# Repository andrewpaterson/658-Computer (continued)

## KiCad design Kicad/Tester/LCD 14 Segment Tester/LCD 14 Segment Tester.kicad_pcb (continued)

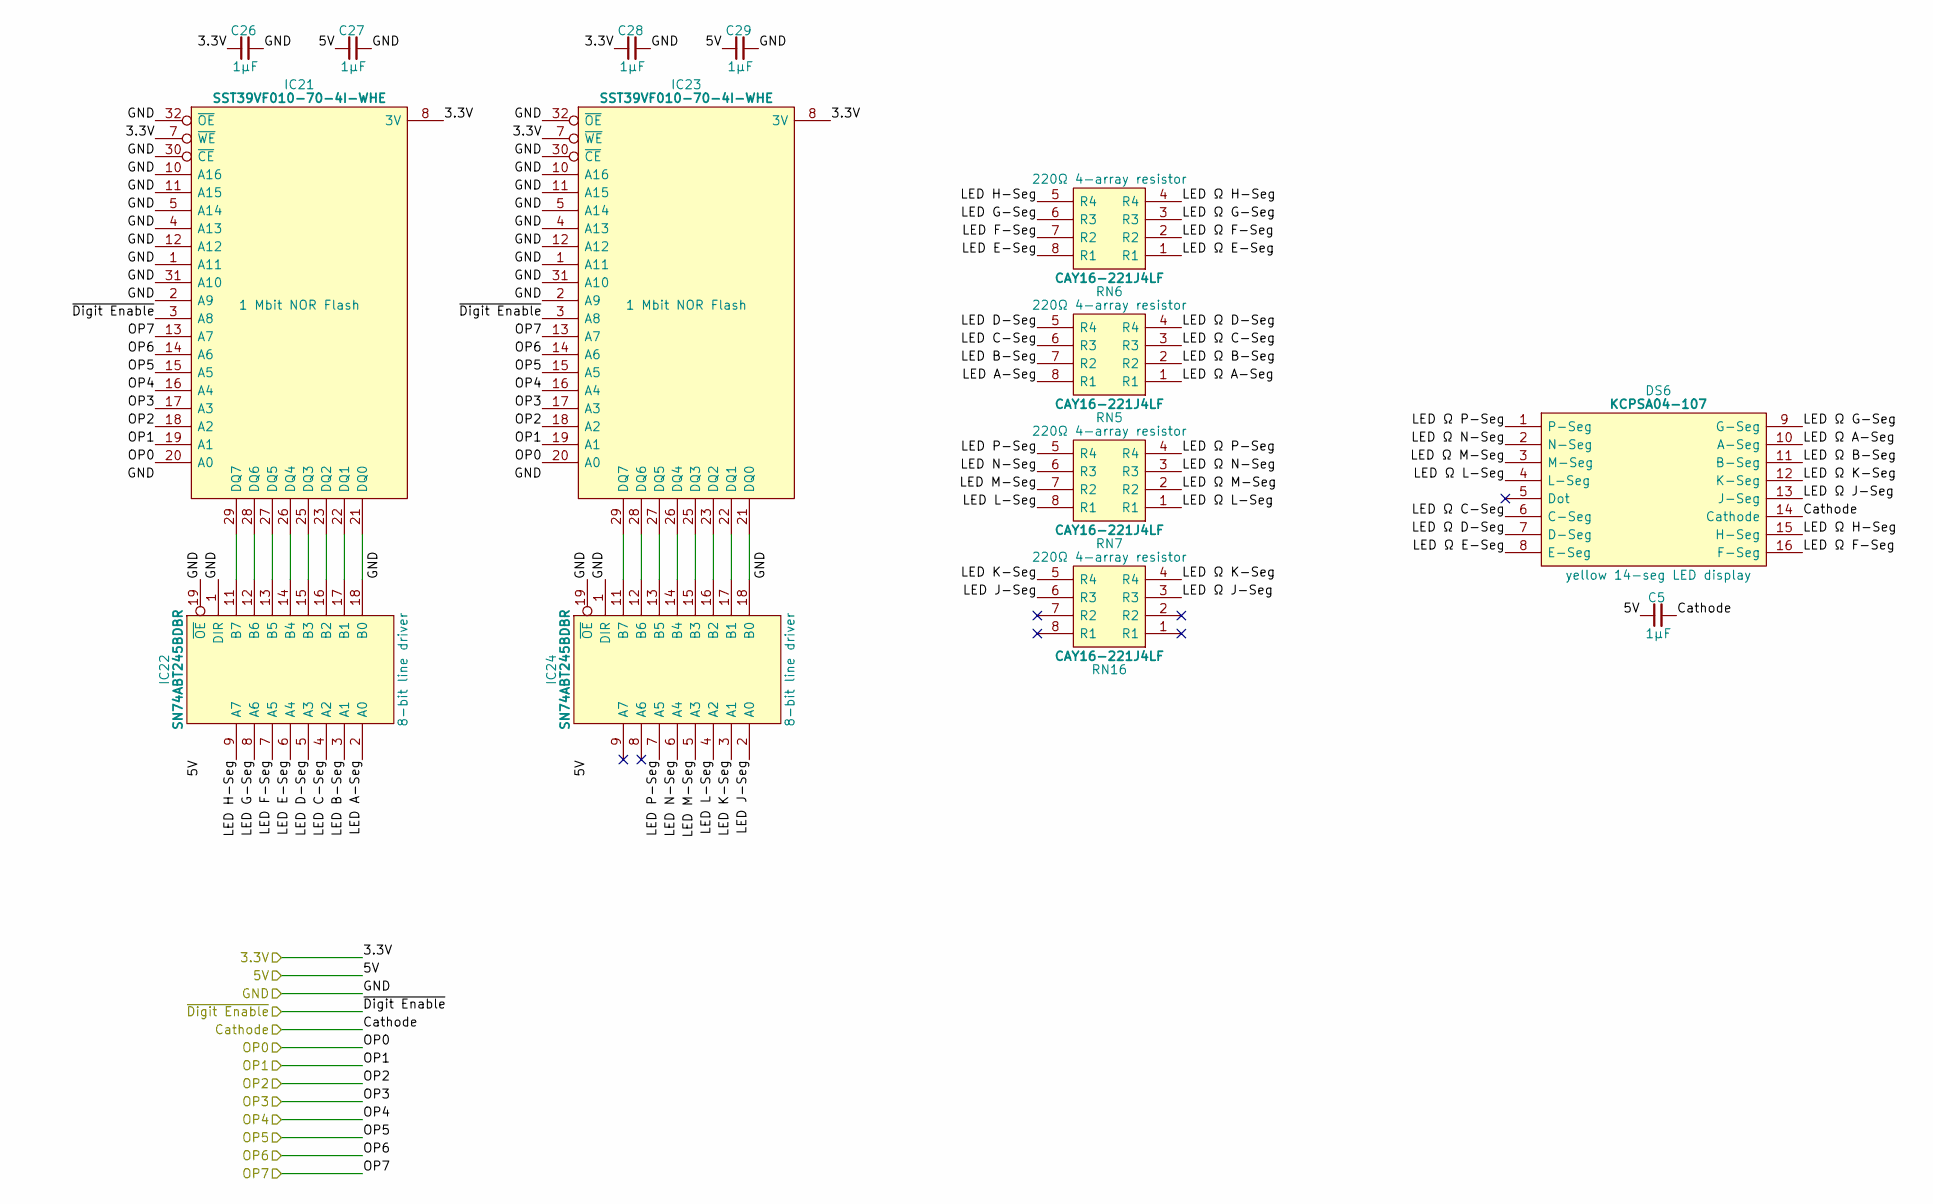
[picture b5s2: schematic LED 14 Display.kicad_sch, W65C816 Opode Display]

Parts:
C5, C26, C27, C28, C29: 1μF; C_0805
DS6: KCPSA04-107; KCPSA04107; Manufacturer_Part_Number KCPSA04-107; Mouser Part Number N/A
IC21, IC23: SST39VF010-70-4I-WHE; DIP-32_TSSOP_14mm_Adapter; Manufacturer_Part_Number SST39VF010-70-4I-WHE-T; Mouser Part Number 579-39VF0107IWHET
IC22, IC24: SN74ABT245BDBR; SOP65P780X200-20N; Manufacturer_Part_Number SN74ABT245BDBR; Mouser Part Number 595-SN74ABT245BDBR
RN5, RN6, RN7, RN16: CAY16-221J4LF; CAY16-F4; Manufacturer_Part_Number CAY16-221J4LF; Mouser Part Number 652-CAY16-221J4LF

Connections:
/3.3V: C26.1, C28.1, IC21.7 (~WE), IC21.8 (3V), IC23.7 (~WE), IC23.8 (3V); also elsewhere on the board
/5V: C5.1, C27.1, C29.1, IC22.20 (5V), IC24.20 (5V); also elsewhere on the board
/GND: C5.2, C26.2, C27.2, C28.2, C29.2, DS6.14 (Cathode), IC21.1 (A11), IC21.2 (A9), IC21.3 (A8), IC21.4 (A13), IC21.5 (A14), IC21.10 (A16), IC21.11 (A15), IC21.12 (A12), IC21.24 (GND), IC21.30 (~CE), IC21.31 (A10), IC21.32 (~OE), IC22.1 (DIR), IC22.10 (GND), IC22.19 (~OE), IC23.1 (A11), IC23.2 (A9), IC23.3 (A8), IC23.4 (A13), IC23.5 (A14), IC23.10 (A16), IC23.11 (A15), IC23.12 (A12), IC23.24 (GND), IC23.30 (~CE), IC23.31 (A10), IC23.32 (~OE), IC24.1 (DIR), IC24.10 (GND), IC24.19 (~OE); also elsewhere on the board
/Left Opcode/LED A-Seg: IC22.2 (A0), RN5.8 (R1)
/Left Opcode/LED B-Seg: IC22.3 (A1), RN5.7 (R2)
/Left Opcode/LED C-Seg: IC22.4 (A2), RN5.6 (R3)
/Left Opcode/LED D-Seg: IC22.5 (A3), RN5.5 (R4)
/Left Opcode/LED E-Seg: IC22.6 (A4), RN6.8 (R1)
/Left Opcode/LED F-Seg: IC22.7 (A5), RN6.7 (R2)
/Left Opcode/LED G-Seg: IC22.8 (A6), RN6.6 (R3)
/Left Opcode/LED H-Seg: IC22.9 (A7), RN6.5 (R4)
/Left Opcode/LED J-Seg: IC24.2 (A0), RN16.6 (R3)
/Left Opcode/LED K-Seg: IC24.3 (A1), RN16.5 (R4)
/Left Opcode/LED L-Seg: IC24.4 (A2), RN7.8 (R1)
/Left Opcode/LED M-Seg: IC24.5 (A3), RN7.7 (R2)
/Left Opcode/LED N-Seg: IC24.6 (A4), RN7.6 (R3)
/Left Opcode/LED P-Seg: IC24.7 (A5), RN7.5 (R4)
/Left Opcode/LED Ω A-Seg: DS6.10 (A-Seg), RN5.1 (R1)
/Left Opcode/LED Ω B-Seg: DS6.11 (B-Seg), RN5.2 (R2)
/Left Opcode/LED Ω C-Seg: DS6.6 (C-Seg), RN5.3 (R3)
/Left Opcode/LED Ω D-Seg: DS6.7 (D-Seg), RN5.4 (R4)
/Left Opcode/LED Ω E-Seg: DS6.8 (E-Seg), RN6.1 (R1)
/Left Opcode/LED Ω F-Seg: DS6.16 (F-Seg), RN6.2 (R2)
/Left Opcode/LED Ω G-Seg: DS6.9 (G-Seg), RN6.3 (R3)
/Left Opcode/LED Ω H-Seg: DS6.15 (H-Seg), RN6.4 (R4)
/Left Opcode/LED Ω J-Seg: DS6.13 (J-Seg), RN16.3 (R3)
/Left Opcode/LED Ω K-Seg: DS6.12 (K-Seg), RN16.4 (R4)
/Left Opcode/LED Ω L-Seg: DS6.4 (L-Seg), RN7.1 (R1)
/Left Opcode/LED Ω M-Seg: DS6.3 (M-Seg), RN7.2 (R2)
/Left Opcode/LED Ω N-Seg: DS6.2 (N-Seg), RN7.3 (R3)
/Left Opcode/LED Ω P-Seg: DS6.1 (P-Seg), RN7.4 (R4)
unnamed: IC21.21 (DQ0), IC22.18 (B0)
unnamed: IC21.22 (DQ1), IC22.17 (B1)
unnamed: IC21.23 (DQ2), IC22.16 (B2)
unnamed: IC21.25 (DQ3), IC22.15 (B3)
unnamed: IC21.26 (DQ4), IC22.14 (B4)
unnamed: IC21.27 (DQ5), IC22.13 (B5)
unnamed: IC21.28 (DQ6), IC22.12 (B6)
unnamed: IC21.29 (DQ7), IC22.11 (B7)
unnamed: IC23.21 (DQ0), IC24.18 (B0)
unnamed: IC23.22 (DQ1), IC24.17 (B1)
unnamed: IC23.23 (DQ2), IC24.16 (B2)
unnamed: IC23.25 (DQ3), IC24.15 (B3)
unnamed: IC23.26 (DQ4), IC24.14 (B4)
unnamed: IC23.27 (DQ5), IC24.13 (B5)
unnamed: IC23.28 (DQ6), IC24.12 (B6)
unnamed: IC23.29 (DQ7), IC24.11 (B7)
OP0: IC21.20 (A0), IC23.20 (A0); also elsewhere on the board
OP1: IC21.19 (A1), IC23.19 (A1); also elsewhere on the board
OP2: IC21.18 (A2), IC23.18 (A2); also elsewhere on the board
OP3: IC21.17 (A3), IC23.17 (A3); also elsewhere on the board
OP4: IC21.16 (A4), IC23.16 (A4); also elsewhere on the board
OP5: IC21.15 (A5), IC23.15 (A5); also elsewhere on the board
OP6: IC21.14 (A6), IC23.14 (A6); also elsewhere on the board
OP7: IC21.13 (A7), IC23.13 (A7); also elsewhere on the board

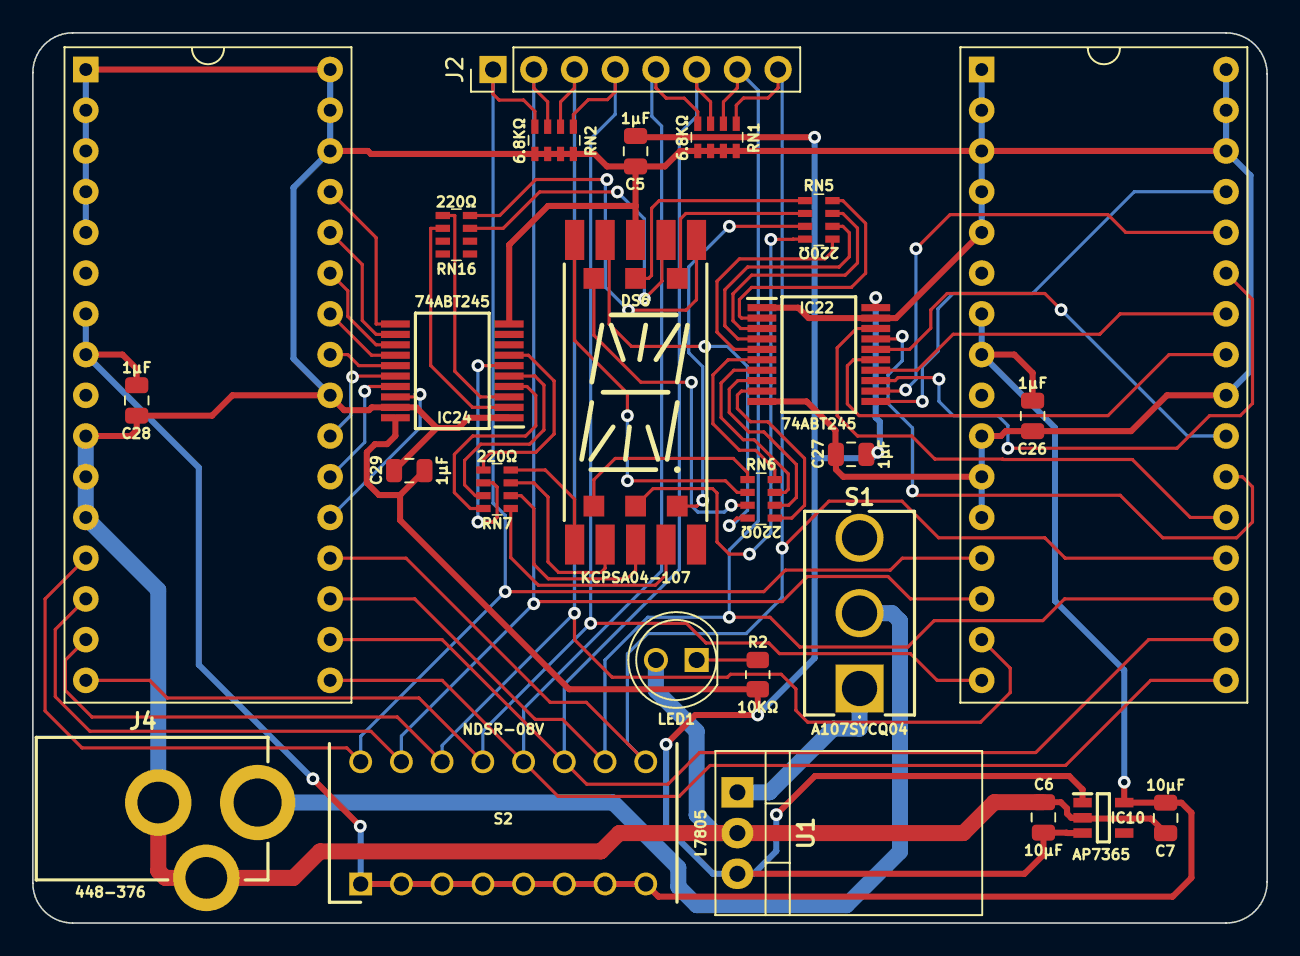
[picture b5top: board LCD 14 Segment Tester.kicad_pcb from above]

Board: 2 copper layers, 77.0 x 55.5 mm, 26 parts (0 on the bottom side), 58 nets.

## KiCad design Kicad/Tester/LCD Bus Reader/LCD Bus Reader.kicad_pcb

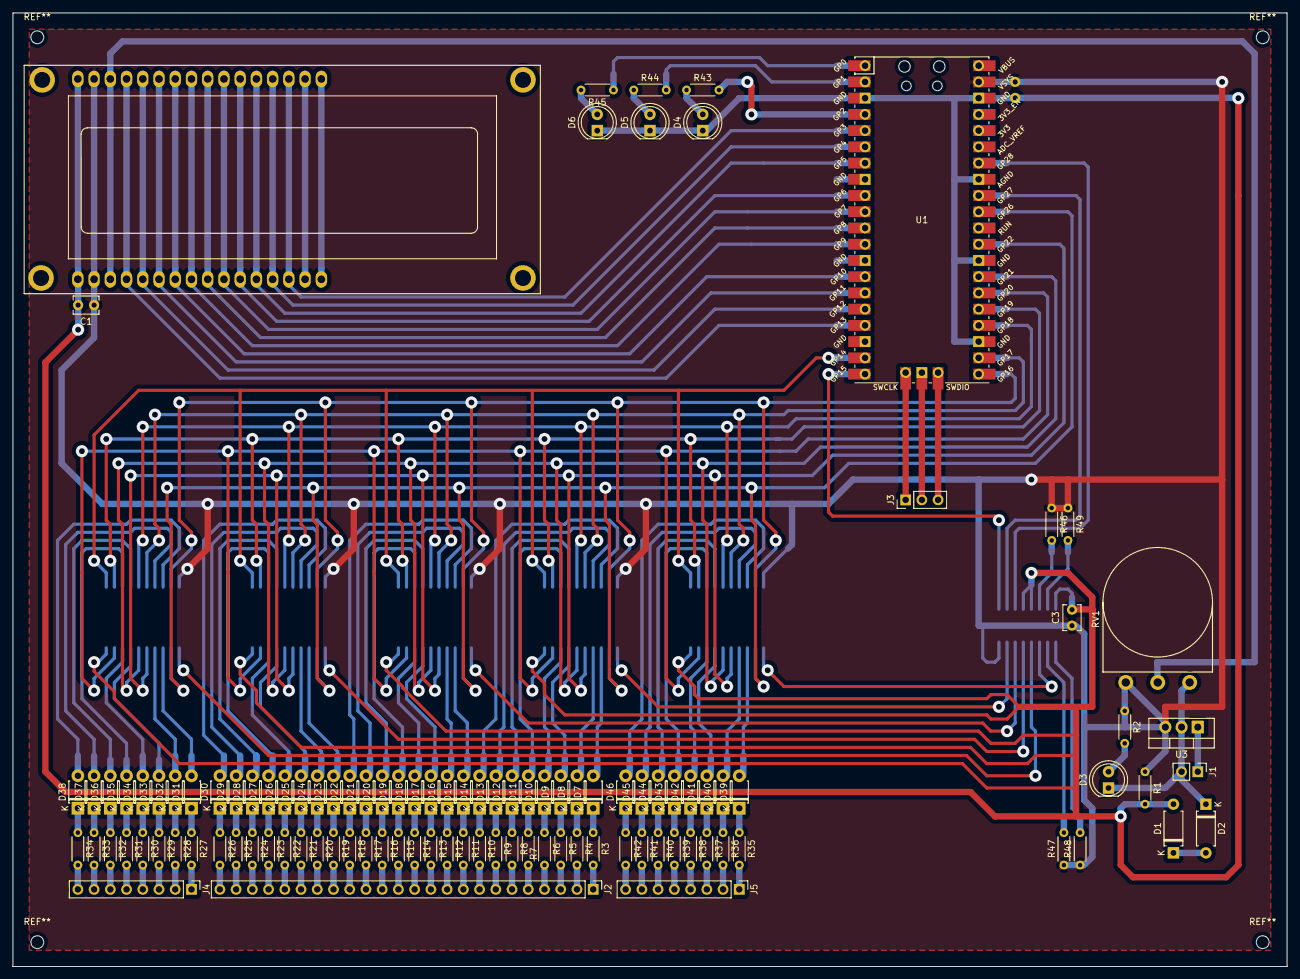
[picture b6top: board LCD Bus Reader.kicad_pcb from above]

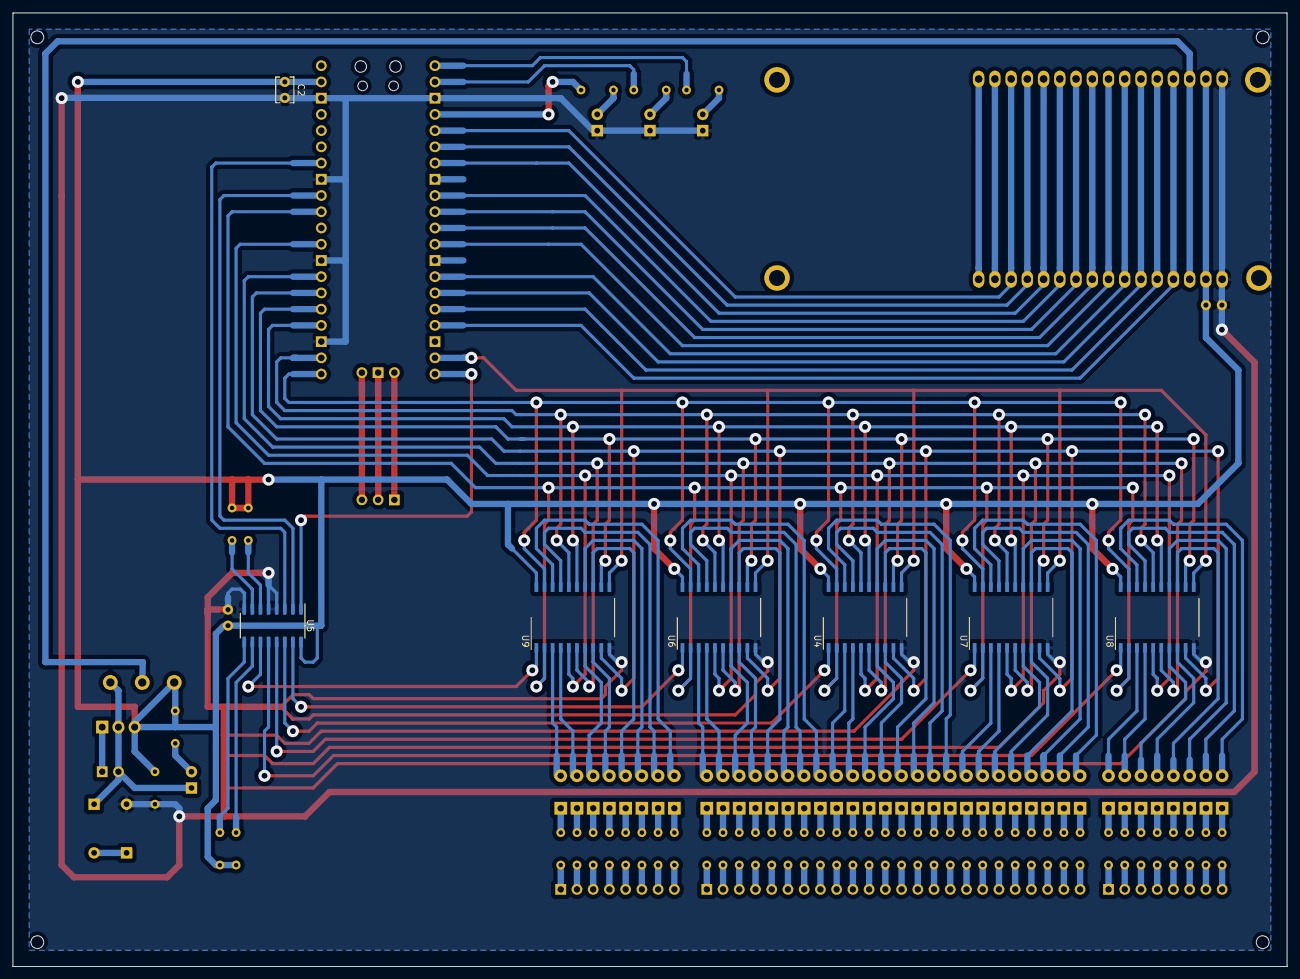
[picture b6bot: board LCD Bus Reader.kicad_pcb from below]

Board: 2 copper layers, 199.4 x 149.2 mm, 113 parts (7 on the bottom side), 168 nets.

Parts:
C1, C2, C3: C; C_Disc_D3.8mm_W2.6mm_P2.50mm
D1, D2: D_Zener; D_A-405_P7.62mm_Horizontal
D3, D4, D5, D6: LED; LED_D5.0mm
D7, D8, D9, D10, D11, D12, D13, D14, D15, D16, D17, D18, D19, D20, D21, D22, D23, D24, D25, D26, D27, D28, D29, D30, D31, D32, D33, D34, D35, D36, D37, D38, D39, D40, D41, D42, D43, D44, D45, D46: 1N4148; D_T-1_P5.08mm_Horizontal
J1: Conn_01x02_Male; PinHeader_1x02_P2.54mm_Vertical
J2: Conn_01x24_Male; PinHeader_1x24_P2.54mm_Vertical
J3: Conn_01x03_Male; PinHeader_1x03_P2.54mm_Vertical
J4, J5: Conn_01x08_Male; PinHeader_1x08_P2.54mm_Vertical
R1, R2, R3, R4, R5, R6, R7, R8, R9, R10, R11, R12, R13, R14, R15, R16, R17, R18, R19, R20, R21, R22, R23, R24, R25, R26, R27, R28, R29, R30, R31, R32, R33, R34, R35, R36, R37, R38, R39, R40, R41, R42, R43, R44, R45, R46, R47, R48, R49: R; R_Axial_DIN0204_L3.6mm_D1.6mm_P5.08mm_Horizontal
RV1: R_POT; Potentiometer_Omeg_PC16BU_Vertical
U1: Pico; RPi_Pico_SMD_TH
U2: RC1602A; NMTC-S16205
U3: L7805; TO-220-3_Vertical
U4, U6, U7, U8, U9: 74LS373; SO-20_12.8x7.5mm_P1.27mm
U5: 74LS138; SO-16_3.9x9.9mm_P1.27mm

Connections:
+12V: J1.1, U3.1
/0V: D2.1, D3.1, J1.2, RV1.1, U3.2
/1.6V: C1.2, C2.2, C3.2, D1.2, D4.1, D5.1, D6.1, R1.2, U1.3, U1.23, U1.28, U1.33, U1.38, U2.1, U4.10, U5.4, U5.5, U5.8, U6.10, U7.10, U8.10, U9.10
/5V: C1.1, C2.1, C3.1, R1.1, R2.1, R46.1, R47.1, R48.1, R49.1, RV1.3, U1.39, U2.2, U3.3, U4.20, U5.16, U6.20, U7.20, U8.20, U9.20
/CE0: U5.15, U6.1
/CE1: U4.1, U5.14
/CE2: U5.13, U7.1
/CE3: U5.12, U8.1
/CE4: U5.11, U9.1
/CE5: R47.2, U5.10
/CE6: R48.2, U5.9
/CE7: R49.2, U5.7
/CS0: U1.20, U5.1
/CS1: U1.32, U5.2
/CS2: U1.34, U5.3
/DB0: U1.14, U2.7
/DB1: U1.12, U2.8
/DB2: U1.11, U2.9
/DB3: U1.10, U2.10
/DB4: U1.9, U2.11
/DB5: U1.7, U2.12
/DB6: U1.6, U2.13
/DB7: U1.5, U2.14
/DET3: R46.2, U5.6
/E: U1.15, U2.6
/L0: U1.31, U4.2, U6.2, U7.2, U8.2, U9.2
/L1: U1.29, U4.5, U6.5, U7.5, U8.5, U9.5
/L2: U1.27, U4.6, U6.6, U7.6, U8.6, U9.6
/L3: U1.26, U4.9, U6.9, U7.9, U8.9, U9.9
/L4: U1.25, U4.12, U6.12, U7.12, U8.12, U9.12
/L5: U1.24, U4.15, U6.15, U7.15, U8.15, U9.15
/L6: U1.22, U4.16, U6.16, U7.16, U8.16, U9.16
/L7: U1.21, U4.19, U6.19, U7.19, U8.19, U9.19
/LE: U1.19, U4.11, U6.11, U7.11, U8.11, U9.11
/P1: D7.2, U6.3
/P2: D8.2, U6.4
/P3: D9.2, U6.7
/P4: D10.2, U6.8
/P5: D11.2, U6.13
/P6: D12.2, U6.14
/P7: D13.2, U6.17
/P8: D14.2, U6.18
/P9: D15.2, U4.3
/P10: D16.2, U4.4
/P11: D17.2, U4.7
/P12: D18.2, U4.8
/P13: D19.2, U4.13
/P14: D20.2, U4.14
/P15: D21.2, U4.17
/P16: D22.2, U4.18
/P17: D23.2, U7.3
/P18: D24.2, U7.4
/P19: D25.2, U7.7
/P20: D26.2, U7.8
/P21: D27.2, U7.13
/P22: D28.2, U7.14
/P23: D29.2, U7.17
/P24: D30.2, U7.18
/P25: D31.2, U8.3
/P26: D32.2, U8.4
/P27: D33.2, U8.7
/P28: D34.2, U8.8
/P29: D35.2, U8.13
/P30: D36.2, U8.14
/P31: D37.2, U8.17
/P32: D38.2, U8.18
/P33: D39.2, U9.3
/P34: D40.2, U9.4
/P35: D41.2, U9.7
/P36: D42.2, U9.8
/P37: D43.2, U9.13
/P38: D44.2, U9.14
/P39: D45.2, U9.17
/P40: D46.2, U9.18
/RS: U1.17, U2.4
/RW: U1.16, U2.5
/V0: RV1.2, U2.3
unnamed: D1.1, D2.2
unnamed: D3.2, R2.2
unnamed: D4.2, R43.1
unnamed: D5.2, R44.1
unnamed: D6.2, R45.2
unnamed: D7.1, R3.1
unnamed: D8.1, R4.1
unnamed: D9.1, R5.1
unnamed: D10.1, R6.1
unnamed: D11.1, R7.1
unnamed: D12.1, R8.1
unnamed: D13.1, R9.1
unnamed: D14.1, R10.1
unnamed: D15.1, R11.1
unnamed: D16.1, R12.1
unnamed: D17.1, R13.1
unnamed: D18.1, R14.1
unnamed: D19.1, R15.1
unnamed: D20.1, R16.1
unnamed: D21.1, R17.1
unnamed: D22.1, R18.1
unnamed: D23.1, R19.1
unnamed: D24.1, R20.1
unnamed: D25.1, R21.1
unnamed: D26.1, R22.1
unnamed: D27.1, R23.1
unnamed: D28.1, R24.1
unnamed: D29.1, R25.1
unnamed: D30.1, R26.1
unnamed: D31.1, R27.1
unnamed: D32.1, R28.1
unnamed: D33.1, R29.1
unnamed: D34.1, R30.1
unnamed: D35.1, R31.1
unnamed: D36.1, R32.1
unnamed: D37.1, R33.1
unnamed: D38.1, R34.1
unnamed: D39.1, R35.1
unnamed: D40.1, R36.1
unnamed: D41.1, R37.1
unnamed: D42.1, R38.1
unnamed: D43.1, R39.1
unnamed: D44.1, R40.1
unnamed: D45.1, R41.1
unnamed: D46.1, R42.1
unnamed: J2.1, R3.2
unnamed: J2.2, R4.2
unnamed: J2.3, R5.2
unnamed: J2.4, R6.2
unnamed: J2.5, R7.2
unnamed: J2.6, R8.2
unnamed: J2.7, R9.2
unnamed: J2.8, R10.2
unnamed: J2.9, R11.2
unnamed: J2.10, R12.2
unnamed: J2.11, R13.2
unnamed: J2.12, R14.2
unnamed: J2.13, R15.2
unnamed: J2.14, R16.2
unnamed: J2.15, R17.2
unnamed: J2.16, R18.2
unnamed: J2.17, R19.2
unnamed: J2.18, R20.2
unnamed: J2.19, R21.2
unnamed: J2.20, R22.2
unnamed: J2.21, R23.2
unnamed: J2.22, R24.2
unnamed: J2.23, R25.2
unnamed: J2.24, R26.2
unnamed: J3.1, U1.41
unnamed: J3.2, U1.42
unnamed: J3.3, U1.43
unnamed: J4.1, R27.2
unnamed: J4.2, R28.2
unnamed: J4.3, R29.2
unnamed: J4.4, R30.2
unnamed: J4.5, R31.2
unnamed: J4.6, R32.2
unnamed: J4.7, R33.2
unnamed: J4.8, R34.2
unnamed: J5.1, R35.2
unnamed: J5.2, R36.2
unnamed: J5.3, R37.2
unnamed: J5.4, R38.2
unnamed: J5.5, R39.2
unnamed: J5.6, R40.2
unnamed: J5.7, R41.2
unnamed: J5.8, R42.2
unnamed: R43.2, U1.4
unnamed: R44.2, U1.2
unnamed: R45.1, U1.1

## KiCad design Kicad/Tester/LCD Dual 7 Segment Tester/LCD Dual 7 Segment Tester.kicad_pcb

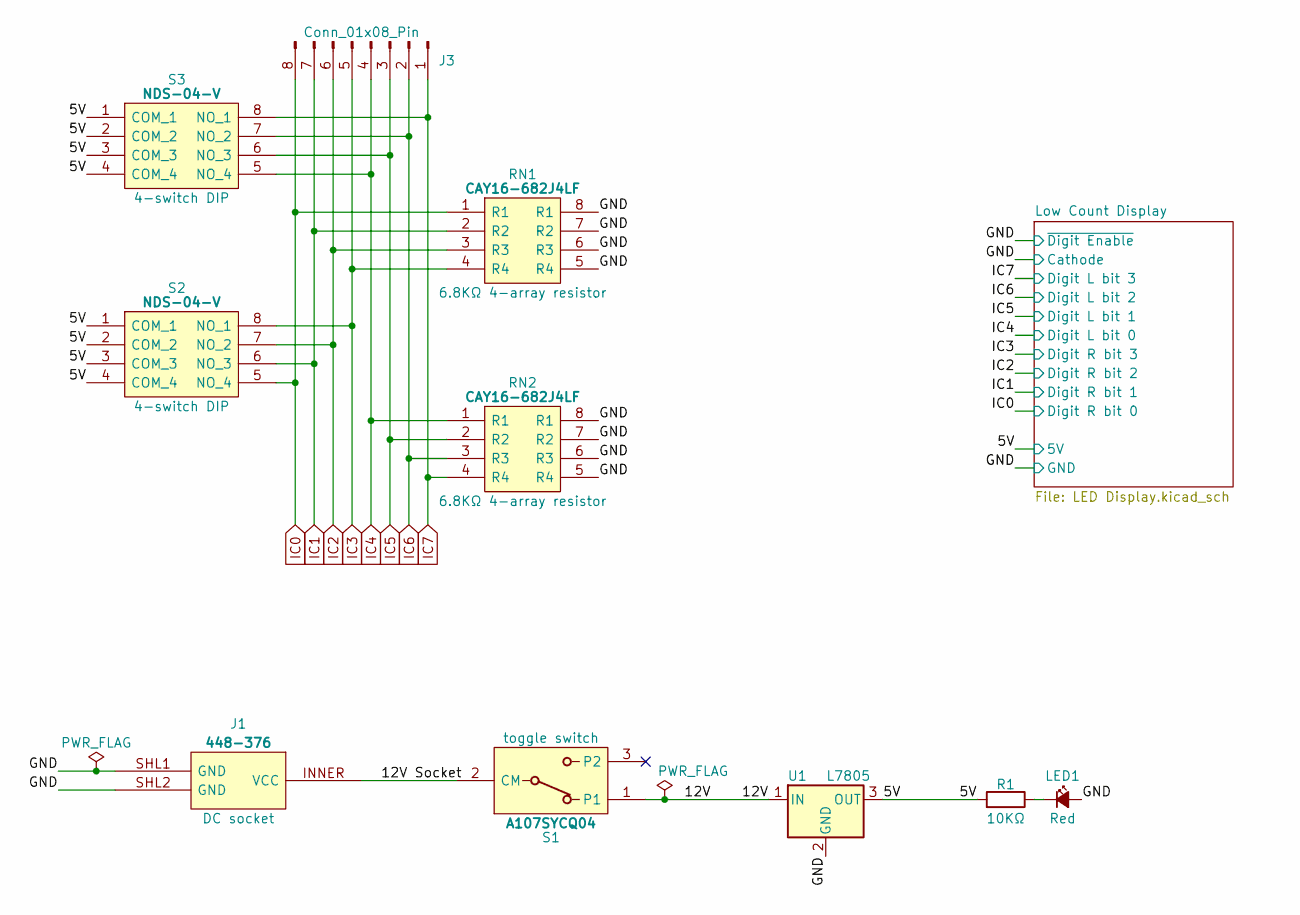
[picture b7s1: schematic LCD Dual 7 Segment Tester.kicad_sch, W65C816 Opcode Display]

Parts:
J1: 448-376; 448376; Manufacturer_Part_Number 448-376
J3: Conn_01x08_Pin; PinHeader_1x08_P2.54mm_Vertical
LED1: Red; LED_D5.0mm
R1: 10KΩ; R_DIN_P7.62mm
RN1, RN2: CAY16-682J4LF; CAY16-J4
S1: A107SYCQ04; Manufacturer_Part_Number A107SYCQ04; Mouser Part Number 506-5-1825137-1
S2, S3: NDS-04-V; NDS04V; Manufacturer_Part_Number NDS-04-V; Mouser Part Number 642-DS04
U1: L7805; TO-220-3_Vertical

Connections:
/5V: R1.2, S2.1 (COM_1), S2.2 (COM_2), S2.3 (COM_3), S2.4 (COM_4), S3.1 (COM_1), S3.2 (COM_2), S3.3 (COM_3), S3.4 (COM_4), U1.3 (OUT); also elsewhere on the board
/12V: S1.1, U1.1 (IN)
/12V Socket: J1.INNER (VCC), S1.2 (CM)
/GND: J1.SHL1 (GND), J1.SHL2 (GND), LED1.2 (A), RN1.5 (R4), RN1.6 (R3), RN1.7 (R2), RN1.8 (R1), RN2.5 (R4), RN2.6 (R3), RN2.7 (R2), RN2.8 (R1), U1.2 (GND); also elsewhere on the board
IC0: J3.8, RN1.1 (R1), S2.5 (NO_4); also elsewhere on the board
IC1: J3.7, RN1.2 (R2), S2.6 (NO_3); also elsewhere on the board
IC2: J3.6, RN1.3 (R3), S2.7 (NO_2); also elsewhere on the board
IC3: J3.5, RN1.4 (R4), S2.8 (NO_1); also elsewhere on the board
IC4: J3.4, RN2.1 (R1), S3.5 (NO_4); also elsewhere on the board
IC5: J3.3, RN2.2 (R2), S3.6 (NO_3); also elsewhere on the board
IC6: J3.2, RN2.3 (R3), S3.7 (NO_2); also elsewhere on the board
IC7: J3.1, RN2.4 (R4), S3.8 (NO_1); also elsewhere on the board
unnamed: LED1.1 (K), R1.1

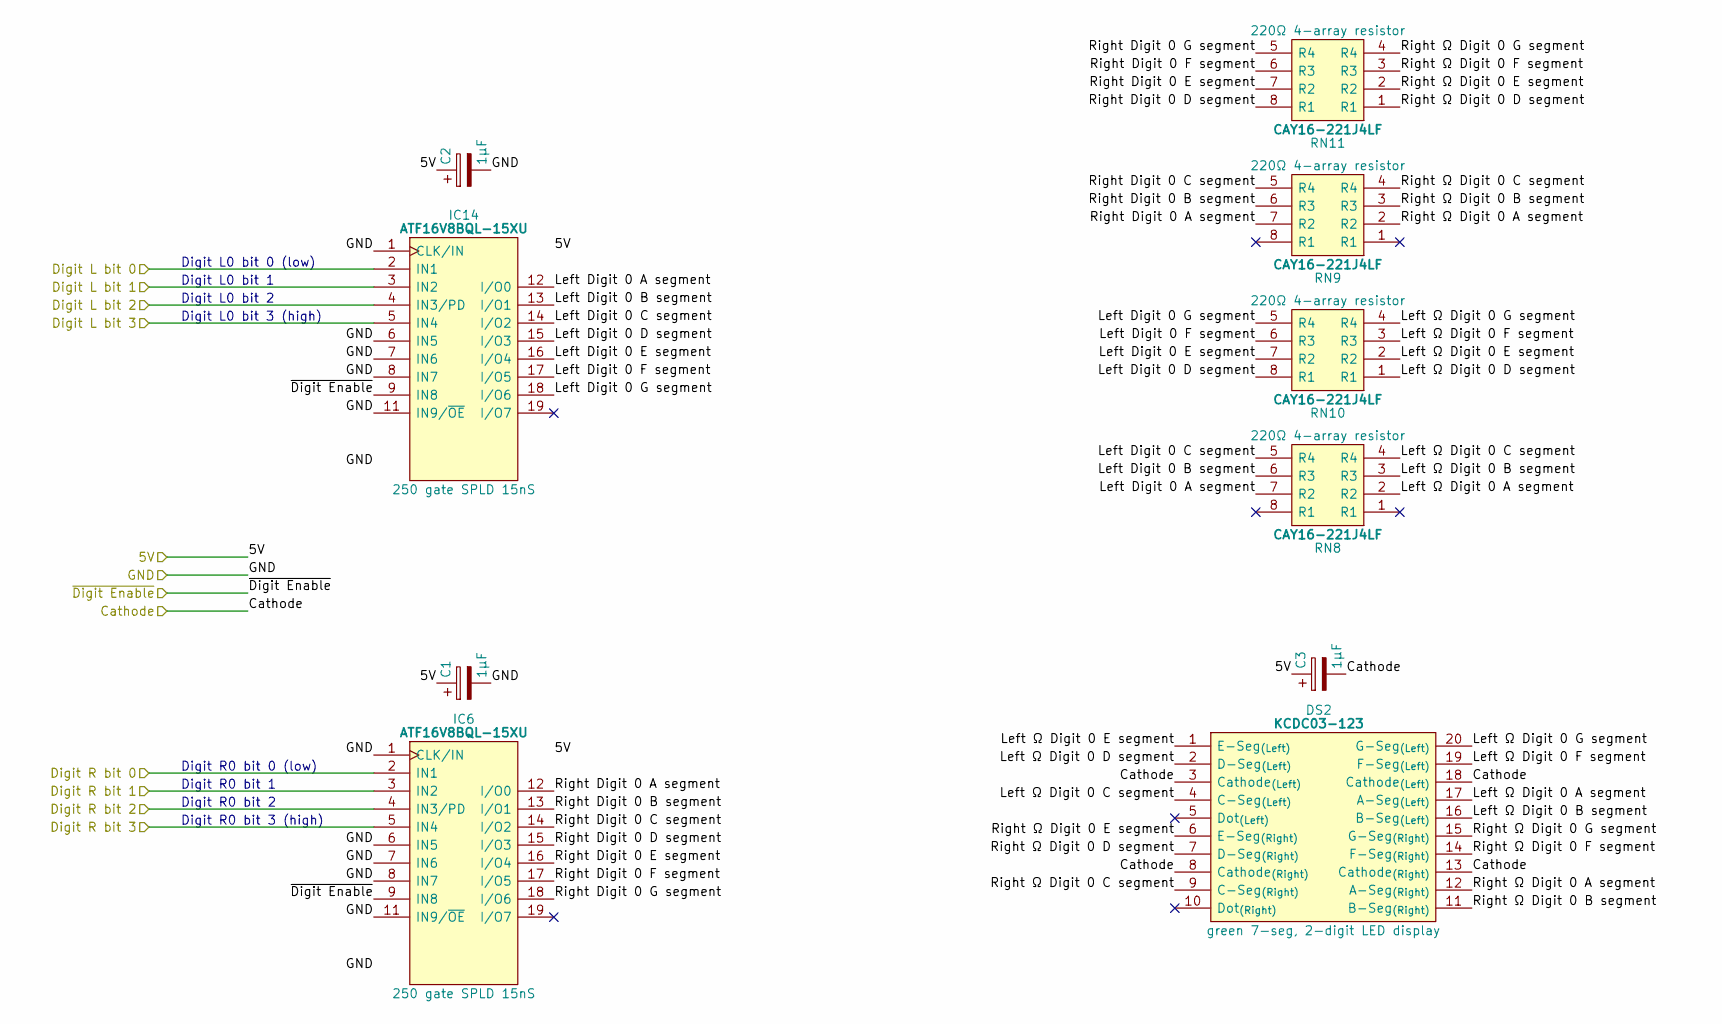
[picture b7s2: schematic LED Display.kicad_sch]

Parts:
C1, C2, C3: 1μF; CP_Radial_D4.0mm_P2.00mm
DS2: KCDC03-123; KCDC03123; Manufacturer_Part_Number KCDC03-123; Mouser Part Number N/A
IC6, IC14: ATF16V8BQL-15XU; DIP-20_W15.24mm_Socket; Manufacturer_Part_Number ATF16V8BQL-15XU; Mouser Part Number 556-AF16V8BQL15XU
RN8, RN9, RN10, RN11: CAY16-221J4LF; CAY16-F4; Manufacturer_Part_Number CAY16-221J4LF; Mouser Part Number 652-CAY16-221J4LF

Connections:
/5V: C1.1, C2.1, C3.1, IC6.20 (5V), IC14.20 (5V); also elsewhere on the board
/GND: C1.2, C2.2, C3.2, DS2.3 (Cathode_{(Left)}), DS2.8 (Cathode_{(Right)}), DS2.13 (Cathode_{(Right)}), DS2.18 (Cathode_{(Left)}), IC6.1 (CLK/IN), IC6.6 (IN5), IC6.7 (IN6), IC6.8 (IN7), IC6.9 (IN8), IC6.10 (GND), IC6.11 (IN9/~OE), IC14.1 (CLK/IN), IC14.6 (IN5), IC14.7 (IN6), IC14.8 (IN7), IC14.9 (IN8), IC14.10 (GND), IC14.11 (IN9/~OE); also elsewhere on the board
/Low Count Display/Left Digit 0 A segment: IC14.12 (I/O0), RN8.7 (R2)
/Low Count Display/Left Digit 0 B segment: IC14.13 (I/O1), RN8.6 (R3)
/Low Count Display/Left Digit 0 C segment: IC14.14 (I/O2), RN8.5 (R4)
/Low Count Display/Left Digit 0 D segment: IC14.15 (I/O3), RN10.8 (R1)
/Low Count Display/Left Digit 0 E segment: IC14.16 (I/O4), RN10.7 (R2)
/Low Count Display/Left Digit 0 F segment: IC14.17 (I/O5), RN10.6 (R3)
/Low Count Display/Left Digit 0 G segment: IC14.18 (I/O6), RN10.5 (R4)
/Low Count Display/Left Ω Digit 0 A segment: DS2.17 (A-Seg_{(Left)}), RN8.2 (R2)
/Low Count Display/Left Ω Digit 0 B segment: DS2.16 (B-Seg_{(Left)}), RN8.3 (R3)
/Low Count Display/Left Ω Digit 0 C segment: DS2.4 (C-Seg_{(Left)}), RN8.4 (R4)
/Low Count Display/Left Ω Digit 0 D segment: DS2.2 (D-Seg_{(Left)}), RN10.1 (R1)
/Low Count Display/Left Ω Digit 0 E segment: DS2.1 (E-Seg_{(Left)}), RN10.2 (R2)
/Low Count Display/Left Ω Digit 0 F segment: DS2.19 (F-Seg_{(Left)}), RN10.3 (R3)
/Low Count Display/Left Ω Digit 0 G segment: DS2.20 (G-Seg_{(Left)}), RN10.4 (R4)
/Low Count Display/Right Digit 0 A segment: IC6.12 (I/O0), RN9.7 (R2)
/Low Count Display/Right Digit 0 B segment: IC6.13 (I/O1), RN9.6 (R3)
/Low Count Display/Right Digit 0 C segment: IC6.14 (I/O2), RN9.5 (R4)
/Low Count Display/Right Digit 0 D segment: IC6.15 (I/O3), RN11.8 (R1)
/Low Count Display/Right Digit 0 E segment: IC6.16 (I/O4), RN11.7 (R2)
/Low Count Display/Right Digit 0 F segment: IC6.17 (I/O5), RN11.6 (R3)
/Low Count Display/Right Digit 0 G segment: IC6.18 (I/O6), RN11.5 (R4)
/Low Count Display/Right Ω Digit 0 A segment: DS2.12 (A-Seg_{(Right)}), RN9.2 (R2)
/Low Count Display/Right Ω Digit 0 B segment: DS2.11 (B-Seg_{(Right)}), RN9.3 (R3)
/Low Count Display/Right Ω Digit 0 C segment: DS2.9 (C-Seg_{(Right)}), RN9.4 (R4)
/Low Count Display/Right Ω Digit 0 D segment: DS2.7 (D-Seg_{(Right)}), RN11.1 (R1)
/Low Count Display/Right Ω Digit 0 E segment: DS2.6 (E-Seg_{(Right)}), RN11.2 (R2)
/Low Count Display/Right Ω Digit 0 F segment: DS2.14 (F-Seg_{(Right)}), RN11.3 (R3)
/Low Count Display/Right Ω Digit 0 G segment: DS2.15 (G-Seg_{(Right)}), RN11.4 (R4)
IC0: IC6.2 (IN1); also elsewhere on the board
IC1: IC6.3 (IN2); also elsewhere on the board
IC2: IC6.4 (IN3/PD); also elsewhere on the board
IC3: IC6.5 (IN4); also elsewhere on the board
IC4: IC14.2 (IN1); also elsewhere on the board
IC5: IC14.3 (IN2); also elsewhere on the board
IC6: IC14.4 (IN3/PD); also elsewhere on the board
IC7: IC14.5 (IN4); also elsewhere on the board

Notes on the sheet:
Digit R0 bit 0 (low)
Digit R0 bit 3 (high)
Digit R0 bit 2
Digit L0 bit 0 (low)
Digit L0 bit 2
Digit R0 bit 1
Digit L0 bit 3 (high)
Digit L0 bit 1

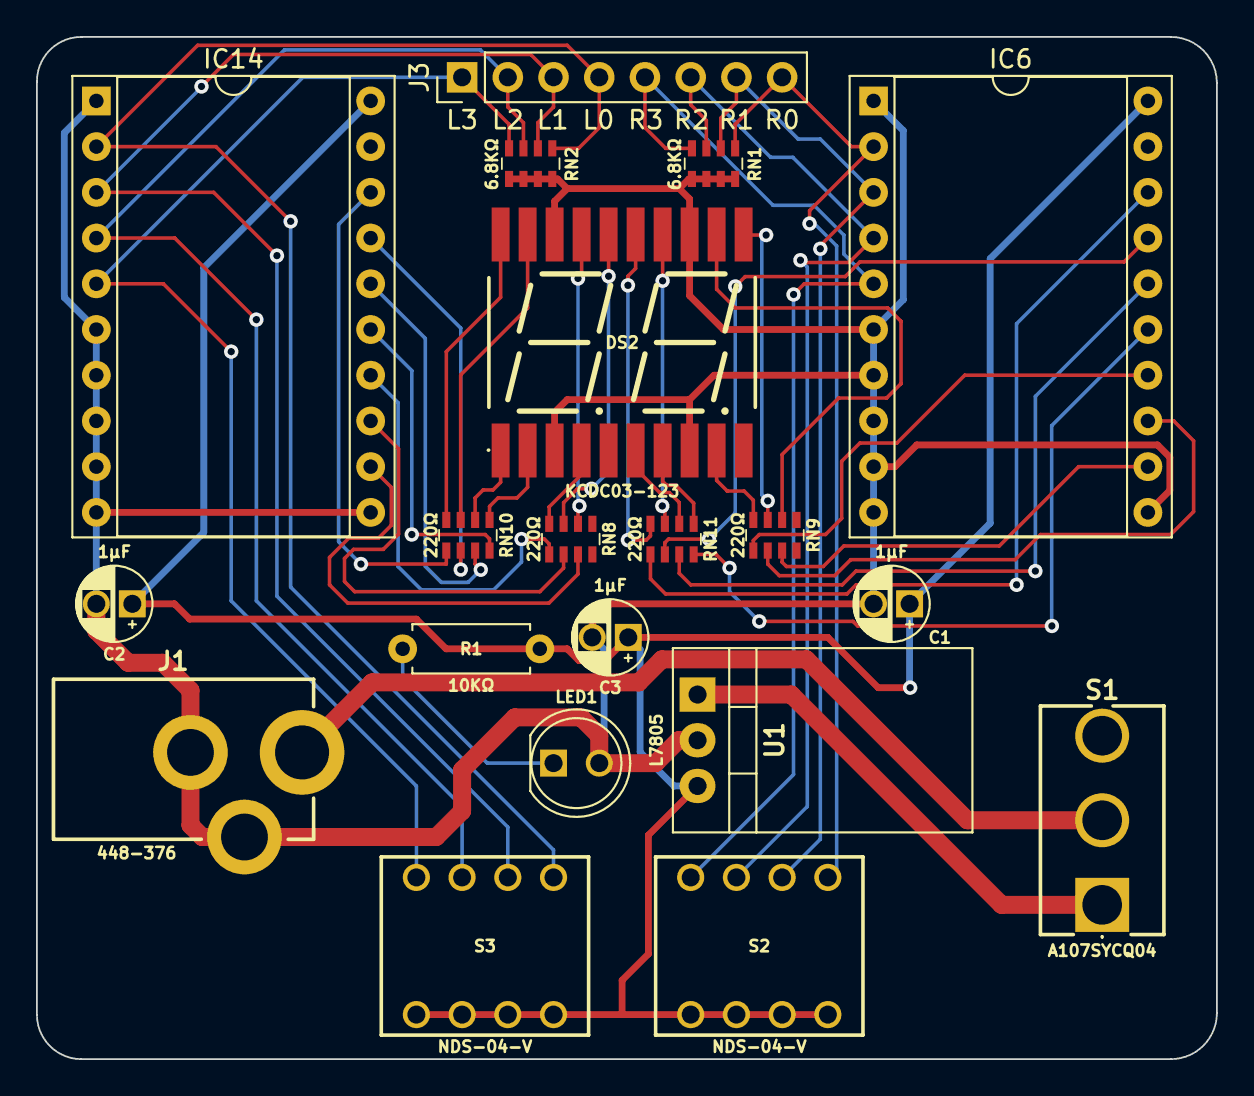
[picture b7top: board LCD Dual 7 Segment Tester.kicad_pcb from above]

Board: 2 copper layers, 65.6 x 56.8 mm, 20 parts (0 on the bottom side), 41 nets.
